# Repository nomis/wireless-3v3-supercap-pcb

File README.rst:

Wireless 3.3V Supercapacitor PCB
================================

Overview
--------

PCB to wirelessly power a 3.3V microcontroller circuit and charge a
supercapacitor so that it keeps running for at least an hour when taken off the
charging coil.

Dimensions: 88mm W × 40mm H

Usage
-----

This is a KiCad project.

Safety
------

There is a toggle switch to discharge the supercapacitor, which will take 14-16
minutes at 390mΩ (unverified). This process is limited by the current switching
capacity of the switch.

Schematics
----------

.. image:: render/wireless-3v3-supercap-Root-sch.svg
   :alt: Root schematic

Power In
~~~~~~~~

.. image:: render/wireless-3v3-supercap-Power%20In-sch.svg
   :alt: Power in schematic

Charge
~~~~~~

.. image:: render/wireless-3v3-supercap-Charge-sch.svg
   :alt: Charge schematic

Power Out
~~~~~~~~~

Output power is supplied at 3.3V up to 3A, from a supercapacitor voltage range
of 0.5-2.7V.

.. image:: render/wireless-3v3-supercap-Power%20Out-sch.svg
   :alt: Power out schematic

PCB
---

.. image:: render/wireless-3v3-supercap-pcb.svg
   :alt: PCB

Components
----------

+---------------------+----------+--------------------------------------------------------------+
| Refs                | Quantity | Name                                                         |
+=====================+==========+==============================================================+
| C.C0                |     1    | 22pF 10% 16V X7R Capacitor, SMD 0805 (Metric 2012)           |
+---------------------+----------+--------------------------------------------------------------+
| C.C1, C.C6, C.10,   |     4    | 0.1µF 10% 16V X7R Capacitor, SMD 0805 (Metric 2012)          |
| C.C11               |          |                                                              |
+---------------------+----------+--------------------------------------------------------------+
| C.C4, C.C5, C.C7    |     3    | 1µF 10% 16V X7R Capacitor, SMD 0805 (Metric 2012)            |
+---------------------+----------+--------------------------------------------------------------+
| C.C8, C.C9, P.C1    |     3    | 10µF 10% 16V X7R Capacitor, SMD 0805 (Metric 2012)           |
+---------------------+----------+--------------------------------------------------------------+
| C.C12               |     1    | 15µF 10% 16V X7R Capacitor, SMD 0805 (Metric 2012)           |
+---------------------+----------+--------------------------------------------------------------+
| M.C1                |     1    | Tecate TPLH-2R7/800PS35X71 800F 2.7V Capacitor, Through Hole |
+---------------------+----------+--------------------------------------------------------------+
| P.C2, P.C2          |     2    | 22µF 10% 10V X7R Capacitor, SMD 1206 (Metric 3216)           |
+---------------------+----------+--------------------------------------------------------------+
| C.D1                |     1    | Diotec BAT54 30V 200mA Zener Diode, SOT-23-3                 |
+---------------------+----------+--------------------------------------------------------------+
| M.J1                |     1    | 1x05 Pin Header, Through Hole (2.54mm)                       |
+---------------------+----------+--------------------------------------------------------------+
| C.L1                |     1    | Bourns SRN5040-100M 10µH 20% 2.1A Power Inductor             |
+---------------------+----------+--------------------------------------------------------------+
| P.L1                |     1    | Bourns SRP1245A-1R0M 1µH 20% 29A Power Inductor              |
+---------------------+----------+--------------------------------------------------------------+
| C.Q4, C.Q5          |     2    | Vishay SiS412DN N-Channel 30V 12A MOSFET, PowerPAK 1212-8    |
+---------------------+----------+--------------------------------------------------------------+
| M.R2                |     1    | 1kΩ 1% 125mW Resistor, SMD 0805 (Metric 2012)                |
+---------------------+----------+--------------------------------------------------------------+
| C.R0                |     1    | 10mΩ 0.1% 1W Resistor, SMD 0805 (Metric 2012)                |
+---------------------+----------+--------------------------------------------------------------+
| C.R1                |     1    | 305kΩ 0.1% 125mW Resistor, SMD 0805 (Metric 2012)            |
+---------------------+----------+--------------------------------------------------------------+
| C.R2                |     1    | 86.6kΩ 0.1% 125mW Resistor, SMD 0805 (Metric 2012)           |
+---------------------+----------+--------------------------------------------------------------+
| C.R5                |     1    | 100Ω 0.1% 125mW Resistor, SMD 0805 (Metric 2012)             |
+---------------------+----------+--------------------------------------------------------------+
| C.R6                |     1    | 10Ω 1% 125mW Resistor, SMD 0805 (Metric 2012)                |
+---------------------+----------+--------------------------------------------------------------+
| C.R7                |     1    | 100kΩ 0.1% 125mW Resistor, SMD 0805 (Metric 2012)            |
+---------------------+----------+--------------------------------------------------------------+
| C.R8                |     1    | 11.1kΩ 0.1% 125mW Resistor, SMD 0805 (Metric 2012)           |
+---------------------+----------+--------------------------------------------------------------+
| P.R1                |     1    | 402kΩ 0.1% 125mW Resistor, SMD 0805 (Metric 2012)            |
+---------------------+----------+--------------------------------------------------------------+
| P.R2                |     1    | 88.7kΩ 0.1% 125mW Resistor, SMD 0805 (Metric 2012)           |
+---------------------+----------+--------------------------------------------------------------+
| P.R3, P.R4          |     2    | 10kΩ 1% 125mW Resistor, SMD 0805 (Metric 2012)               |
+---------------------+----------+--------------------------------------------------------------+
| M.SW1               |     1    | C&K E103SYZGE SPDT Toggle Switch 7.5A 125V                   |
+---------------------+----------+--------------------------------------------------------------+
| C.TH1               |     1    | 1x02 Pin Header, Through Hole (2.54mm)                       |
|                     |     1    | Semitec 103AT-4-70261 10kΩ 1% Thermistor                     |
+---------------------+----------+--------------------------------------------------------------+
| C.U1                |     1    | Texas Instruments BQ24640RVAR Super Capacitor Charger        |
+---------------------+----------+--------------------------------------------------------------+
| P.U1                |     1    | Texas Instruments TPS61022 8A Boost Converter, 0.5-5.5V      |
+---------------------+----------+--------------------------------------------------------------+
|                     |     1    | Vishay IWAS4832AEEB120KF1 Wireless Charging Receive Coil     |
+---------------------+----------+--------------------------------------------------------------+

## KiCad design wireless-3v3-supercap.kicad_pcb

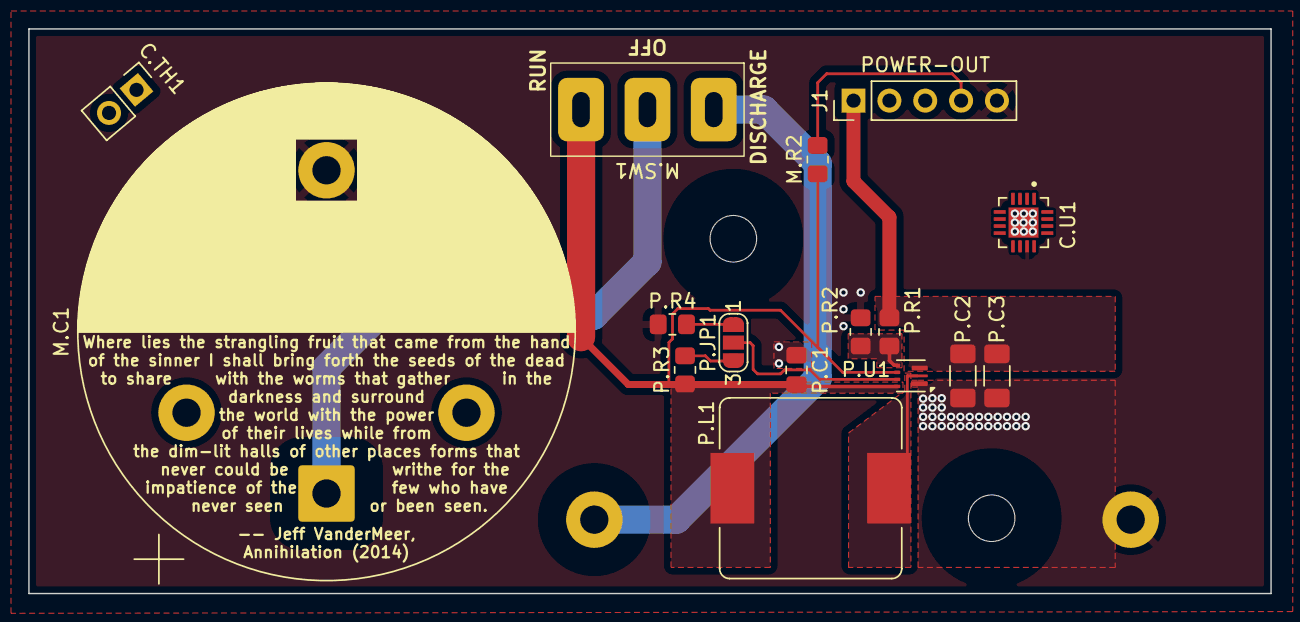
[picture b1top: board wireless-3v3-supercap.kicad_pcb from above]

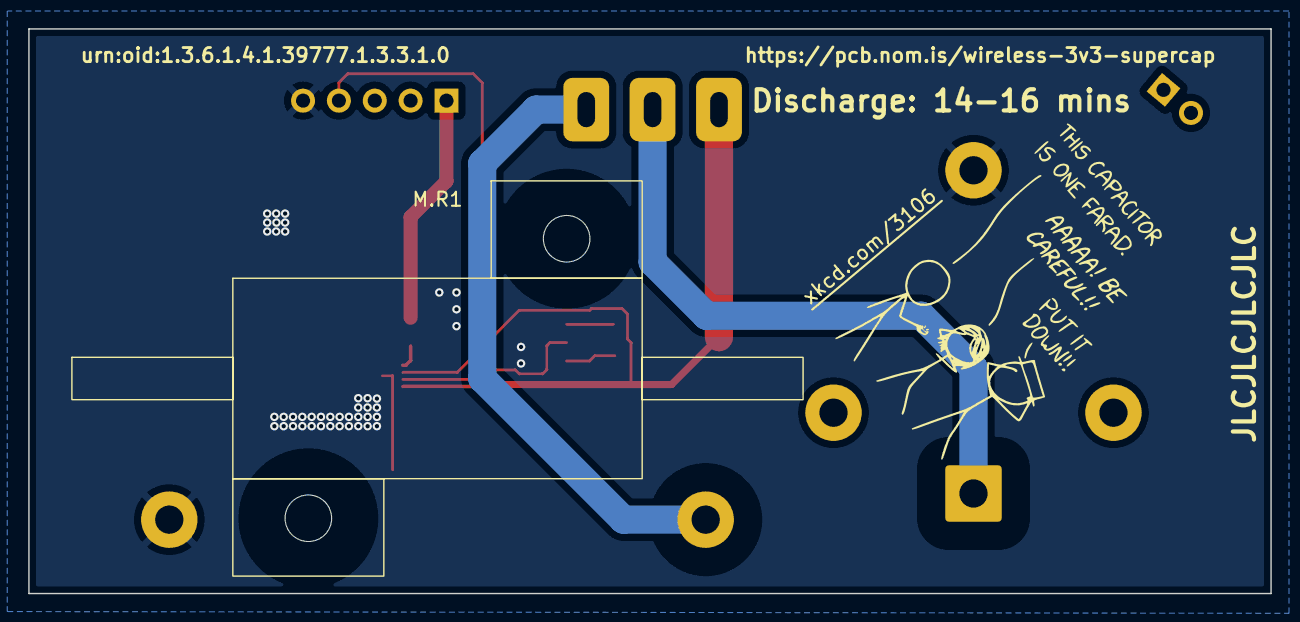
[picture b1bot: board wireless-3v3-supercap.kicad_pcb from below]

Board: 2 copper layers, 88.0 x 40.0 mm, 18 parts (2 on the bottom side), 14 nets.

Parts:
C.TH1: 10kΩ 1%; PinHeader_1x02_P2.54mm_Vertical
C.U1: BQ24640RVAR; QFN50P350X350X100-17N
J1: POWER-OUT; PinHeader_1x05_P2.54mm_Vertical
M.C1: 800F 2.7V; TPLH-2R7_800PS35X71
M.R1: 390mΩ 5% 25W; THS25R39J
M.R2: 1kΩ 1% 125mW; R_0805_2012Metric_Pad1.20x1.40mm_HandSolder
M.SW1: MODE; E103SYZGE
P.C1: 10µF 10% 10V X7R; C_0805_2012Metric_Pad1.18x1.45mm_HandSolder
P.C2, P.C3: 22µF 10% 10V X7R; C_1206_3216Metric_Pad1.33x1.80mm_HandSolder
P.JP1: SolderJumper_2_Open; SolderJumper-3_P1.3mm_Open_RoundedPad1.0x1.5mm_NumberLabels
P.L1: 1µH 25A 30%; L_Bourns_SRP1245A
P.R1: 402kΩ 1% 125mW; R_0805_2012Metric_Pad1.20x1.40mm_HandSolder
P.R2: 88.7kΩ 1% 125mW; R_0805_2012Metric_Pad1.20x1.40mm_HandSolder
P.R3, P.R4: 10kΩ 1% 125mW; R_0805_2012Metric_Pad1.20x1.40mm_HandSolder
P.U1: TPS61022; Texas_RWU0007A_VQFN-7_2x2mm_P0.5mm
XKCD: LOGO

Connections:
+3.3V: J1.1, P.C2.1, P.C3.1, P.R1.1, P.U1.3 (VOUT)
/Charge/SUPERCAP: M.R2.1, M.SW1.3 (4), P.C1.1, P.L1.1, P.R3.1, P.U1.5 (EN), P.U1.7 (VIN)
/DISCHARGE: M.R1.1, M.SW1.1
/Power Out/POWER_FB: P.R1.2, P.R2.1, P.U1.4 (FB)
/Power Out/POWER_SW: P.L1.2, P.U1.2 (SW)
/SUPERCAP: M.C1.1, M.SW1.2 (3)
CAPACITOR_VOLTAGE: J1.4, M.R2.2
CHARGE_STATUS: C.U1.3 (STAT), J1.3
GND: C.U1.11 (GND), C.U1.17 (EP), J1.5, M.C1.2, M.R1.2, P.C1.2, P.C2.2, P.C3.2, P.R2.2, P.R4.2, P.U1.1 (GND)
unnamed: C.U1.2 (CE), C.U1.6 (VREF)
unnamed: P.JP1.1 (A), P.R4.1
unnamed: P.JP1.3 (B), P.R3.2
unnamed: P.JP1.2 (C), P.U1.6 (MODE)
~EXTERNAL_POWER_PRESENT: C.U1.5 (~PG), J1.2

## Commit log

2025-07-11 Add a discharge switch
2025-07-11 Add heatsinks to the discharge resistors
2025-07-11 Show discharge time on the back too
2025-07-11 Move power in pin header out of the way of the resistors
2025-07-13 Add BQ33100PWR
2025-07-13 Add capacitor loss markings
2025-07-13 Move pin headers further away from the edge of the PCB
2025-07-13 Make discharge tracks thicker
2025-07-16 Remove BQ33100PWR and discharge resistors
2025-07-16 Resize PCB to available space
2025-07-16 Add discharge circuit, and main component for charging/power out
2025-07-16 Update expected discharge time
2025-07-16 Configure power output
2025-07-17 Add power output capacitors
2025-07-17 Add inductor and finish power out layout
2025-07-17 Use 1mm traces for 3.3V power output
2025-07-17 Fix schematic links
2025-07-17 Update components list
2025-07-17 Add 3D model for the TPS61022
2025-07-18 Prefix all of the references so that the numbering is manageable across multiple circuits
2025-07-18 Remove charge enable pin
2025-07-18 Connect charger CE to VREF, not VCC
2025-07-19 Combine components under the same reference
2025-07-20 Add voltage divider circuit for ADC
2025-07-20 Fix MOSFET for measuring capacitor voltage
2025-07-20 Mark signals as active low
2025-07-20 Adjust ADC voltage divider
    Increase the value of the 0.5V minimum voltage reading to improve accuracy
2025-07-21 Remove voltage divider circuit for ADC
    The ESP32-C3 can be configured to handle this directly
2025-07-21 Fix pin header name and size
2025-07-22 Add xkcd comic
2025-07-23 Add incomplete charge circuit
2025-07-27 Finish charge circuit
2025-07-27 Center charge schematic
2025-07-27 Add PCB OID and URL
2025-07-27 Add JLC order number text
2025-07-30 Add Area X crawler text quote underneath the topographical anomaly
2025-08-16 Update footprint of THS25R39J
    This measures L=27.3mm M=44.8mm which is much smaller than the maximum
    documented size. Retain the original sizes but move the pads closer
    together to match the connection holes.
2025-08-16 Update footprint of E013SYZGE
    Contacts are 2.1mm wide
